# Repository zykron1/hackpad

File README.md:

# AA Aerospace Hackpad!
Custom macropad with a 3x2 matrix of switches with an OLED display!

## Images 

## BOM
- 1 SEEEDUINO XIAO RP2040
- 6x Cherry MX Switches 
- 4x M3x5x4 Heatset inserts
- 4x M3x10mm Screws
- 1x 0.91" 128x32 OLED Display
- 1x Case
- 1x Top plate

## Build it!
Print the top plate and case files, insert the threaded inserts, drop the pcb in, and screw on the top. Use CircuitPython firmware and flash the main.py file and download the KMK firmware library.

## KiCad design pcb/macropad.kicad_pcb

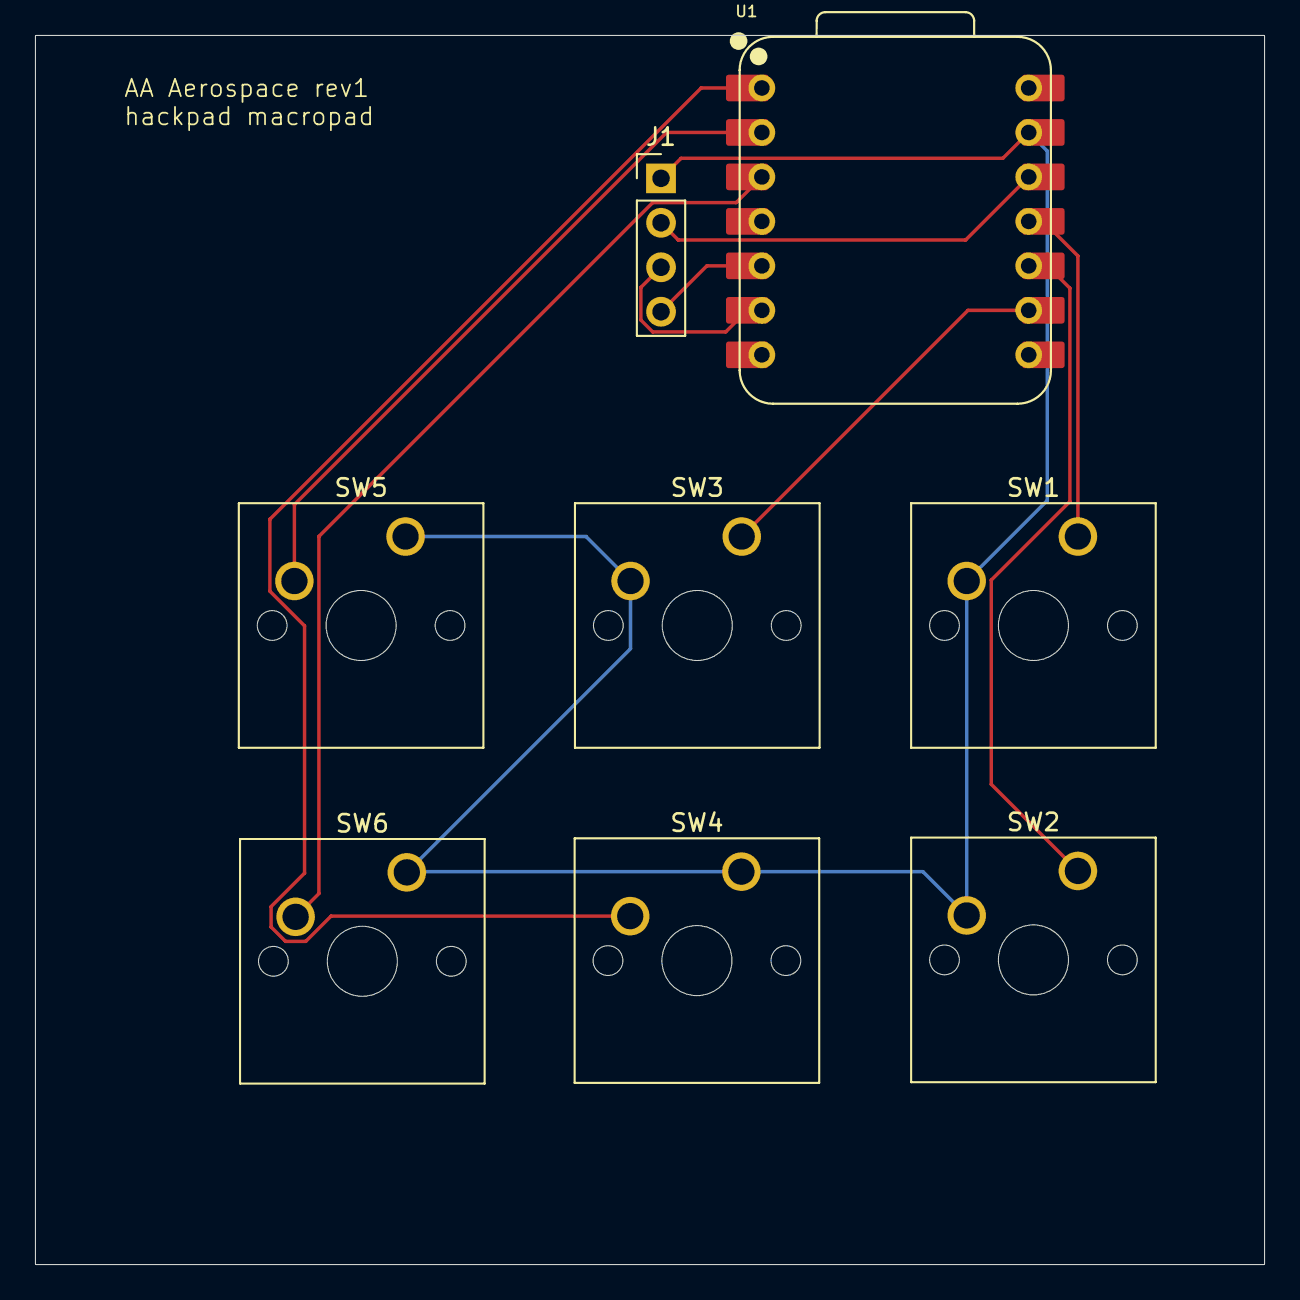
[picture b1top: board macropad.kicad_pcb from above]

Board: 2 copper layers, 70.2 x 70.2 mm, 8 parts (0 on the bottom side), 10 nets.

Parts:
J1: Conn_01x04; PinHeader_1x04_P2.54mm_Vertical
SW1, SW2, SW3, SW4, SW5, SW6: SW_Push; SW_Cherry_MX_1.00u_PCB
U1: XIAO-RP2040-DIP

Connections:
+3V3: J1.2, U1.12 (3V3)
GND: J1.1, SW1.2, SW2.2, SW3.2, SW4.1, SW5.1, SW6.1, U1.13 (GND)
unnamed: J1.3, U1.6 (GPIO7/SCL)
unnamed: J1.4, U1.5 (GPIO6/SDA)
unnamed: SW3.1, U1.9 (GPIO2/SCK)
unnamed: SW1.1, U1.11 (GPIO3/MOSI)
unnamed: SW2.1, U1.10 (GPIO4/MISO)
unnamed: SW4.2, U1.1 (GPIO26/ADC0/A0)
unnamed: SW5.2, U1.2 (GPIO27/ADC1/A1)
unnamed: SW6.2, U1.3 (GPIO28/ADC2/A2)

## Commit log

2025-12-23 readme + cad
2025-12-23 firmware write
